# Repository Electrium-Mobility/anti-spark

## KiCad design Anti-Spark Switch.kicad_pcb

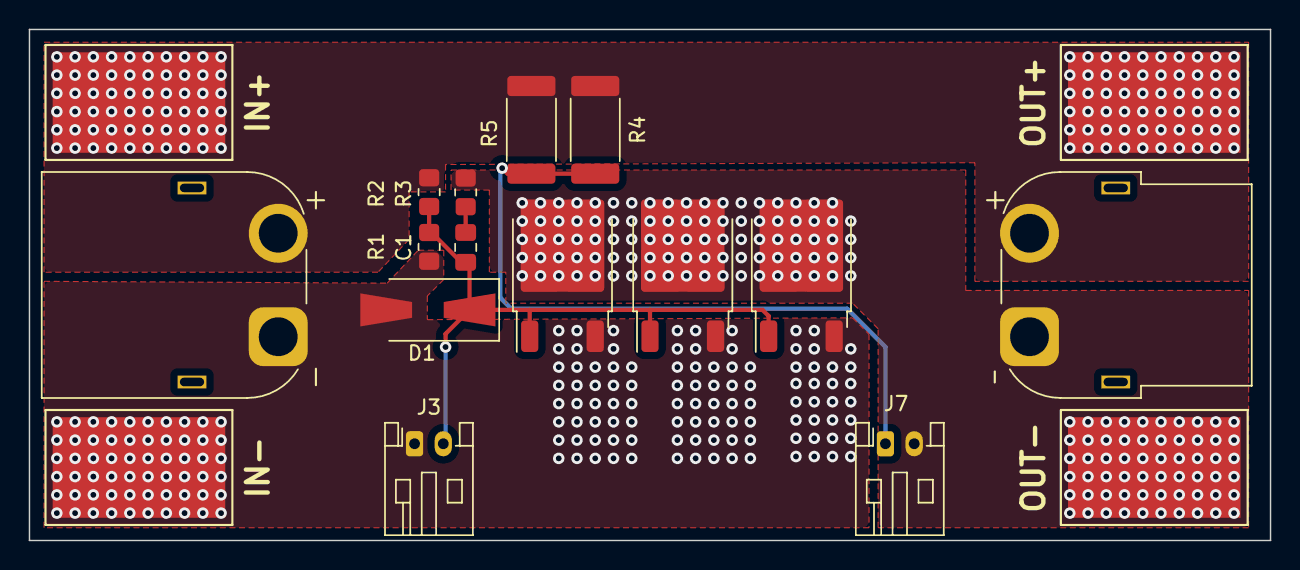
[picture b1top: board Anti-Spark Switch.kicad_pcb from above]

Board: 2 copper layers, 86.4 x 35.6 mm, 18 parts (0 on the bottom side), 6 nets.

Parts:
C1: 1uF; C_0805_2012Metric_Pad1.18x1.45mm_HandSolder
D1: D_Zener; D_SMA-SMB_Universal_Handsoldering
IN+: Conn_01x01; 1PAD_12x7mm
IN-: Conn_01x01; 1PAD_12x7mm
J3, J7: Conn_01x02; JST_PH_S2B-PH-K_1x02_P2.00mm_Horizontal
J5: XT60PW-F; AMASS_XT60PW-F_1x02_P7.20mm_Horizontal
J8: XT60PW-M; AMASS_XT60PW-M_1x02_P7.20mm_Horizontal
OUT+: Conn_01x01; 1PAD_12x7mm
OUT-: Conn_01x01; 1PAD_12x7mm
Q1, Q2, Q3: DMT10H010LK3; TO-252-2
R1, R2: 1M; R_0805_2012Metric_Pad1.20x1.40mm_HandSolder
R3: 1K; R_0805_2012Metric_Pad1.20x1.40mm_HandSolder
R4, R5: 16.5K; R_2512_6332Metric_Pad1.40x3.35mm_HandSolder

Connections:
GND: D1.2 (A), IN-.1, J3.1, J8.1, Q1.3 (S), Q2.3 (S), Q3.3 (S), R1.2
unnamed: C1.1, R3.1
unnamed: C1.2, D1.1 (K), J3.2, Q1.1 (G), Q2.1 (G), Q3.1 (G), R1.1, R2.2
unnamed: J5.1, J7.2, OUT-.1, Q1.2 (D), Q2.2 (D), Q3.2 (D), R3.2
unnamed: J7.1, R4.2, R5.2
VCC: IN+.1, J5.2, J8.2, OUT+.1, R2.1, R4.1, R5.1

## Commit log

2023-05-16 Anti-Spark sch added
2023-07-13 pcb laid out
